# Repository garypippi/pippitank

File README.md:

# Pippitank

ラズパイ戦車制作プロジェクト

- 電源: 2S LiFe (タミヤ LF1100-6.6V)
- Raspberry Piでカメラ連携、リモート操作
- プッシュ型ソレノイドでBB弾発射

```
+----------+
| 2S LiFe  |
+----+-----+
     |
+----+-----------------+  UART  +-----------------------+
| pcb#pippitank-engine +--------+ pcb#pippitank-chassis |
+----+-----------------+        +----+--+-------+-------+
     |       |                       |  |       |
+-------+  +-------+      Dshot#2    |  |       | UART (Slip Ring)
| ESC#1 |  | ESC#2 |-----------------+  |       |
+----+--+  +-------+                    |    +----------------------+
     |                    Dshot#1       |    | pcb#pippitank-turret |
     +----------------------------------+    +----------------------+
                                                |
                                             ?? Planning... ??
```

## コマンド

### ビルド

```sh
cmake -S . -B build
cmake --build build
```

### RPi側

カメラストリーム配信。`--mode 1640:1232` はフル画角化のため（未指定だと中央クロップで約2.5倍ズームになる）:

```sh
rpicam-vid -t 0 --inline \
  --mode 1640:1232 \
  --width 640 --height 480 \
  --framerate 30 --listen -o tcp://0.0.0.0:8888
```

デーモン起動:

```sh
./build/src/pippitankd/pippitankd --listen 0.0.0.0:5000 --serial /dev/ttyS0
```

### ホスト側

操縦に使う入力デバイスの確認:

```sh
ls /dev/input/by-id
```

UI起動。`--log` は省略可（テレメトリCSVを記録する場合のみ）:

```sh
./build/src/pippitank-ui/pippitank-ui \
  --server pippitank:5000 \
  --video tcp://pippitank:8888 \
  --input /dev/input/event8 \
  --log logs/telemetry.csv
```

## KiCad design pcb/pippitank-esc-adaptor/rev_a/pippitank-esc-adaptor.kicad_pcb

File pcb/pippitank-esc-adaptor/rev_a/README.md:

**Known Issues**

1. U/V/Wのキャスタレーションでエッジカットがスルーホールの中心を通っていない

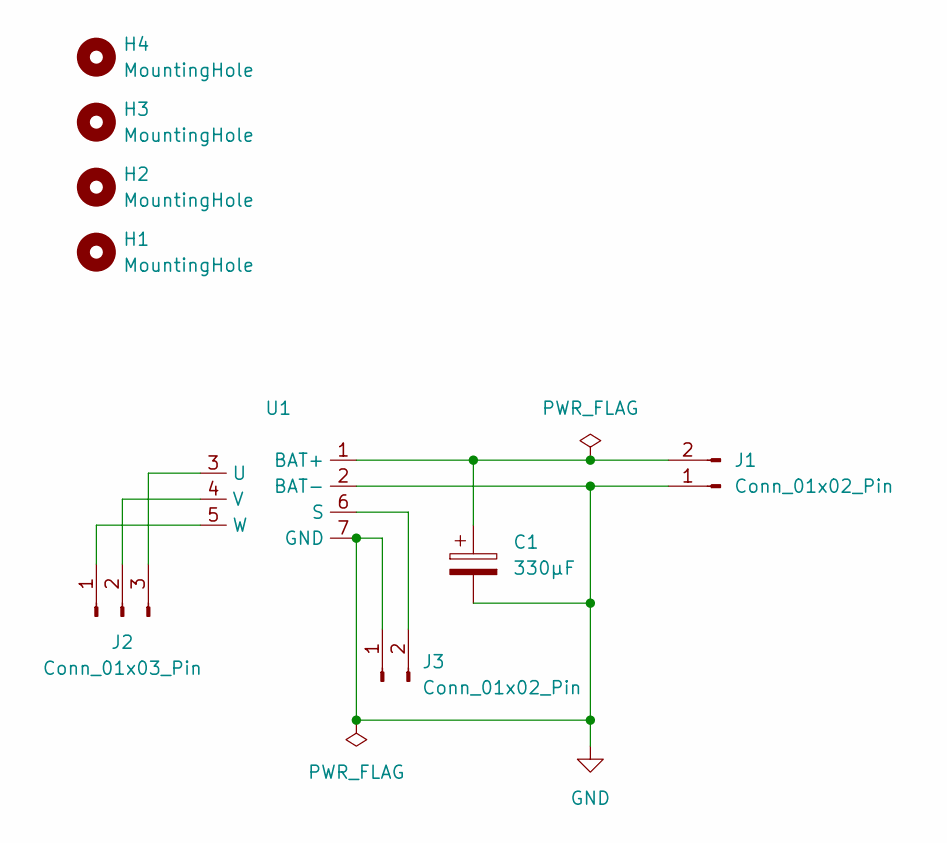
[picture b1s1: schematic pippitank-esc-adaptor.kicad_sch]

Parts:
C1: 330μF; CP_Radial_D10.0mm_P5.00mm
H1, H2, H3, H4: MountingHole; MountingHole_3.2mm_M3
J1: Conn_01x02_Pin; AMASS_XT30PW-M_1x02_P2.50mm_Horizontal
J2: Conn_01x03_Pin; AMASS_MR30PW-M_1x03_P3.50mm_Horizontal
J3: Conn_01x02_Pin; JST_XH_B2B-XH-A_1x02_P2.50mm_Vertical
U1: NOBRAND_ESC_ADAPTOR

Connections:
GND: C1.2, J1.1, J3.1, U1.2 (BAT-), U1.7 (GND)
unnamed: C1.1, J1.2, U1.1 (BAT+)
unnamed: J2.1, U1.5 (W)
unnamed: J2.2, U1.4 (V)
unnamed: J2.3, U1.3 (U)
unnamed: J3.2, U1.6 (S)

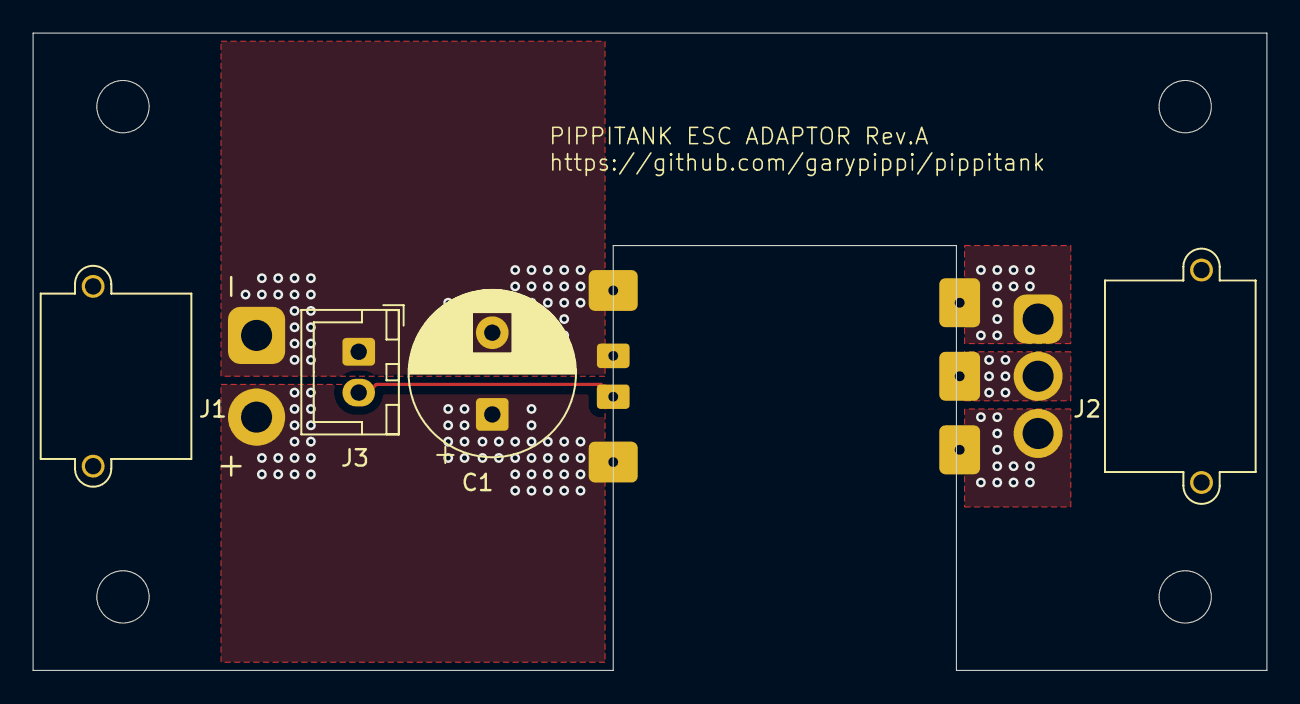
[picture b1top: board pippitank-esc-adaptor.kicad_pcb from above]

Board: 2 copper layers, 75.5 x 39.0 mm, 9 parts (1 on the bottom side), 6 nets.

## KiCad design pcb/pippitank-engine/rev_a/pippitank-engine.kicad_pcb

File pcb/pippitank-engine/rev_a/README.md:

**Known Issues**

1. バランスコネクタのGND,8.4Vが逆
    - JST_XH_3PIN Verticalを逆で実装すること
2. Nch-MOSFETのソースが浮いている
    - SWはON状態で固定すること

## 主要パーツ

- MCU: ATtiny1604
- Pch-MOSFET: TJ60S04M3L
- 電流測定用アンプ: LT6106CS5

## 設計根拠

電力想定

- 各ESCはMAX30A
- システムはMAX5A

## コネクタ

- XT60PW-M: 2S Li-Po
- XT60PW-M: ESC#1
- XT60PW-M: ESC#2
- XT30PW-M: システム#1
- XT30PW-M: システム#2
- JST_XH_3PIN: 2S Li-Po バランスコネクタ
- JST_XH_3PIN: UPDI
- JST_XH_4PIN: UART

## 電流測定 (ESC)

シャント抵抗は1W7mΩ ±5%を調達
並列数は4、 上限30Aとして

- 各抵抗の電流: 7.5A
- 各抵抗の電力: 0.394W
- 電圧降下@30A: 52.5mV
- 必要利得    : 20.95
- 測定誤差@30A: ±0.2A
- 測定誤差@10A: ±2.0%
- 測定誤差@05A: ±4.0%

ADC基準電圧は、精度を優先し1.1Vを使用する。
必要利得は

20.95 = 1100 / 52.5

利得は`ROUT/RIN`で設定する。
RINの範囲にはLT6106内部電流の制約がある。

> 内部電流の上限は1mA、30A時のセンス電圧52.5mVを流すには
> RIN ≥ 52.5mV / 1mA = 52.5Ω
> が必要。
> データシート条件から
> RIN ≤ 500Ω

よって

52.5Ω < RIN < 500Ω

- RIN=240Ω
- ROUT=4.7kΩ (Av≈19.58)
- 出力@30A=1.028V
- 実効FS≈32.1A

出力フィルタは2段LPF構成にする。

- 1段目(LT6106付近): ROUT(4.7kΩ) × COUT1(0.1μF) ≈ 338Hz
    - PWMノイズ(16〜32kHz)を発生源で大幅減衰（-33dB以上）
    - フィルタ後の出力インピーダンスが高周波で低くなり、配線のアンテナ化を抑制
- 2段目(ADC付近): Rs(100Ω) × COUT2(10nF) ≈ 160kHz
    - 長配線で新規に拾ったHFスパイク（FETスイッチング過渡、RF誘導）を叩き落とす
    - ATtiny1604のSAR ADC S/Hキャパへのローカル電荷供給も兼用

```
┌───────┬───────┬──────────────────────────────────────┐
│ 素子  │  値   │                 用途                 │
├───────┼───────┼──────────────────────────────────────┤
│ RIN   │ 240Ω  │ 入力抵抗                             │
├───────┼───────┼──────────────────────────────────────┤
│ ROUT  │ 4.7kΩ │ 出力抵抗（利得設定 兼 1段目LPFのR）  │
├───────┼───────┼──────────────────────────────────────┤
│ COUT1 │ 0.1μF │ ROUT並列、1段目LPFのC（LT6106直近）  │
├───────┼───────┼──────────────────────────────────────┤
│ Rs    │ 100Ω  │ 2段目LPFの直列R（配線途中〜ADC直前） │
├───────┼───────┼──────────────────────────────────────┤
│ COUT2 │ 10nF  │ 2段目LPFのC（ADC直近）               │
└───────┴───────┴──────────────────────────────────────┘
```

**実装時はケルビン接続**

## 電流測定 (システム)

車体、砲塔への電流測定。
負荷はRPi Zero W、RPi Camera、サーボx2、プッシュ型ソレノイド、各MCU

シャント抵抗は1W40mΩ ±1%を調達
並列数は2、 上限5Aとして

- 各抵抗の電流: 2.5A
- 各抵抗の電力: 0.25W (定格50%デレーティング)
- 電圧降下@5A: 100mV
- 必要利得    : 11.0
- 測定誤差@5A: ±1.0%
- 測定誤差@1A: ±5.0%

ADC基準電圧は、精度を優先し1.1Vを使用する。
必要利得は

11.0 = 1100 / 100

- RIN=240Ω
- ROUT=2.4kΩ (Av≈10.0) ※ 2.4kΩは調達しやすい

出力フィルタは2段LPF構成にする。

- 1段目(LT6106付近): ROUT(2.4kΩ) × COUT1(0.1μF) ≈ 663Hz
- 2段目(ADC付近): Rs(100Ω) × COUT2(10nF) ≈ 160kHz

```
┌───────┬───────┬──────────────────────────────────────┐
│ 素子  │  値   │                 用途                 │
├───────┼───────┼──────────────────────────────────────┤
│ RIN   │ 240Ω  │ 入力抵抗                             │
├───────┼───────┼──────────────────────────────────────┤
│ ROUT  │ 2.4kΩ │ 出力抵抗（利得設定 兼 1段目LPFのR）  │
├───────┼───────┼──────────────────────────────────────┤
│ COUT1 │ 0.1μF │ ROUT並列、1段目LPFのC（LT6106直近）  │
├───────┼───────┼──────────────────────────────────────┤
│ Rs    │ 100Ω  │ 2段目LPFの直列R（配線途中〜ADC直前） │
├───────┼───────┼──────────────────────────────────────┤
│ COUT2 │ 10nF  │ 2段目LPFのC（ADC直近）               │
└───────┴───────┴──────────────────────────────────────┘
```

**実装時はケルビン接続**

## 電圧測定

測定地点

1. BATバランス端子: セル#1
2. BAT(+) - BAT(-): 2 - 1 = セル#2電圧
3. post-MOSFETノード - BAT(-): ESC両系統への給電電圧 (Pch-MOSFET ON確認 + 電圧降下モニタ兼用)

抵抗分圧について、精度優先で内蔵基準電圧1.1Vを使用する
MAX8.4として

- (R1+R2)/R2 = 8.4 / 1.1 = 7.64
- R1/R2 = 6.64

R1 = 67kΩ (47kΩ + 20kΩ)
R2 = 10kΩ (8.4V時 1.091V、6.0V時 0.779V)

MAX4.2の場合は R1=47kΩ にすれば良い(4.2V時 0.737V)

LT6106の電流測定と同じく、2段LPF構成で配置する

```
Vin ── R1 ──┬──[配線]── Rs ──┬── ATtiny ADC
            │                │
            R2               C2(10nF)
            │                │
            ├── C1(0.1μF)    GND
            │
           GND
```

- R1, R2, C1 は信号源側に密集させる
  - R2 をMCU側に離すと配線区間が R1=67kΩ の高インピーダンスになり、ノイズを盛大に拾う
  - R1||R2 = 8.7kΩ を信号源側で確立し、低インピーダンス信号を配線に乗せる
- Rs（100Ω）は配線途中〜ADC直前（LT6106と同規格）
  - 2段目LPFの直列R、ADC入力保護
- C2=10nF はADC直近（LT6106のCOUT2と共用規格）
  - 配線で拾ったHFノイズをADC直前でシャント
  - ATtiny1604 SAR ADC のS/Hキャパ充電にも寄与

```
┌───────┬──────────┬──────────────────────────────────────┐
│ 素子  │   値     │               用途                   │
├───────┼──────────┼──────────────────────────────────────┤
│ R1    │ 67kΩ等   │ 分圧上段（信号源側）                 │
├───────┼──────────┼──────────────────────────────────────┤
│ R2    │ 10kΩ     │ 分圧下段（信号源側、R1とセット）     │
├───────┼──────────┼──────────────────────────────────────┤
│ C1    │ 0.1μF    │ R2並列、1段目LPF（信号源側）         │
├───────┼──────────┼──────────────────────────────────────┤
│ Rs    │ 100Ω     │ 2段目LPFの直列R（電流系と共用規格）  │
├───────┼──────────┼──────────────────────────────────────┤
│ C2    │ 10nF     │ 2段目LPF（ADC直近、電流系と共用規格）│
└───────┴──────────┴──────────────────────────────────────┘
```

## 基板温度測定

Pch-MOSFET および シャント抵抗の発熱監視用に NTCサーミスタを1点実装する。

- サーミスタ: NTC 47kΩ ±5% B=4050K ±3% (TDK NTH5G20P40B473J、2012)
- プルアップ: 47kΩ ±5% (NTC R25と対称にして25°C付近の感度最大化、±5%は調達制約・表示用途なら実用上問題なし)
- フィルタ: 2段LPF構成
- ADC参照: VDD(5V) ※この1chのみ、他chは1.1V内部参照のまま

```
VCC(5V) ── R_pu 47kΩ ──┬──[配線]── Rs ──┬── ATtiny ADC (PA7)
                       │                │
                       NTC 47kΩ         C2 (10nF)
                       │                │
                       ├── C1 (0.1μF)   GND
                       │
                       GND
```

温度 vs ADCコード (VDD=5V, 10bit, B=4050K):

```
┌──────┬─────────┬────────┬─────────┐
│ 温度 │ NTC抵抗 │  電圧  │ ADCコード │
├──────┼─────────┼────────┼─────────┤
│ 0°C  │ 163kΩ   │ 3.88V  │  795    │
│ 25°C │ 47kΩ    │ 2.50V  │  512    │
│ 60°C │ 11.3kΩ  │ 0.97V  │  198    │
│ 85°C │ 4.84kΩ  │ 0.47V  │   96    │
│100°C │ 3.06kΩ  │ 0.31V  │   63    │
└──────┴─────────┴────────┴─────────┘
```

Pch-MOSFET裏面の銅箔ベタに密着させ、シャント抵抗発熱も熱結合で捕捉する。
シャットダウン閾値はマージンを取り ADCコード 110 (公称 82°C) 付近で発動、
最悪ケース (B+3%, R25+5%) でも実温度 85°C を超える前に遮断される想定とする。

```
┌───────┬──────────┬─────────────────────────────────────┐
│ 素子  │   値     │               用途                  │
├───────┼──────────┼─────────────────────────────────────┤
│ R_pu  │ 47kΩ ±5% │ プルアップ（信号源側）              │
├───────┼──────────┼─────────────────────────────────────┤
│ NTC   │ 47kΩ     │ NTH5G20P40B473J（信号源側）         │
├───────┼──────────┼─────────────────────────────────────┤
│ C1    │ 0.1μF    │ 1段目LPF（信号源側、NTC並列）       │
├───────┼──────────┼─────────────────────────────────────┤
│ Rs    │ 100Ω     │ 2段目LPFの直列R（全系統共用規格）   │
├───────┼──────────┼─────────────────────────────────────┤
│ C2    │ 10nF     │ 2段目LPF（ADC直近、全系統共用規格） │
└───────┴──────────┴─────────────────────────────────────┘
```

## ATtiny1604

ATtiny1604の消費電力は小さいので、BAT接続時は常に稼働させる

```
BAT(+) ---+---------- (VIN) AP7375 (VOUT) -+--- (A)▷|(K) --- VCC rail --- ATtiny1604
          |                  |             |         D2                   UPDI 5V pin
          | CIN=1μF          |             |
          |                  |             | COUT=10μF
BAT(-) ---+------------------+-------------+
```

- LDO: AP7375(5V300mA)
- 内蔵オシレータ使用
- UPDI引き出し
- 逆流防止ショットキー D2

BAT未接続状態でもArduino Uno経由でUPDI書き込みできるよう、AP7375出力とVCC rail間にショットキーダイオードを挿入する。

- 型番: RB160M-30TR (ROHM, 30V 1A)
- パッケージ: SOD-123F (PMDS、フラットリード)
- VF: 0.43V @ 1A、実動作の~10mA負荷では ~0.2V
- VCC rail電圧: 5.0V - 0.2V ≈ 4.8V（ATtiny動作範囲1.8-5.5V内）

```
AP7375 --+-- (A)▷|(K) ----+----- ATtiny VCC (pin 1)
         |      D2         |
         |                 +--- UPDI header 5V pin
         C2=10μF           |
         |                 C_bypass=0.1μF
        GND               GND
```

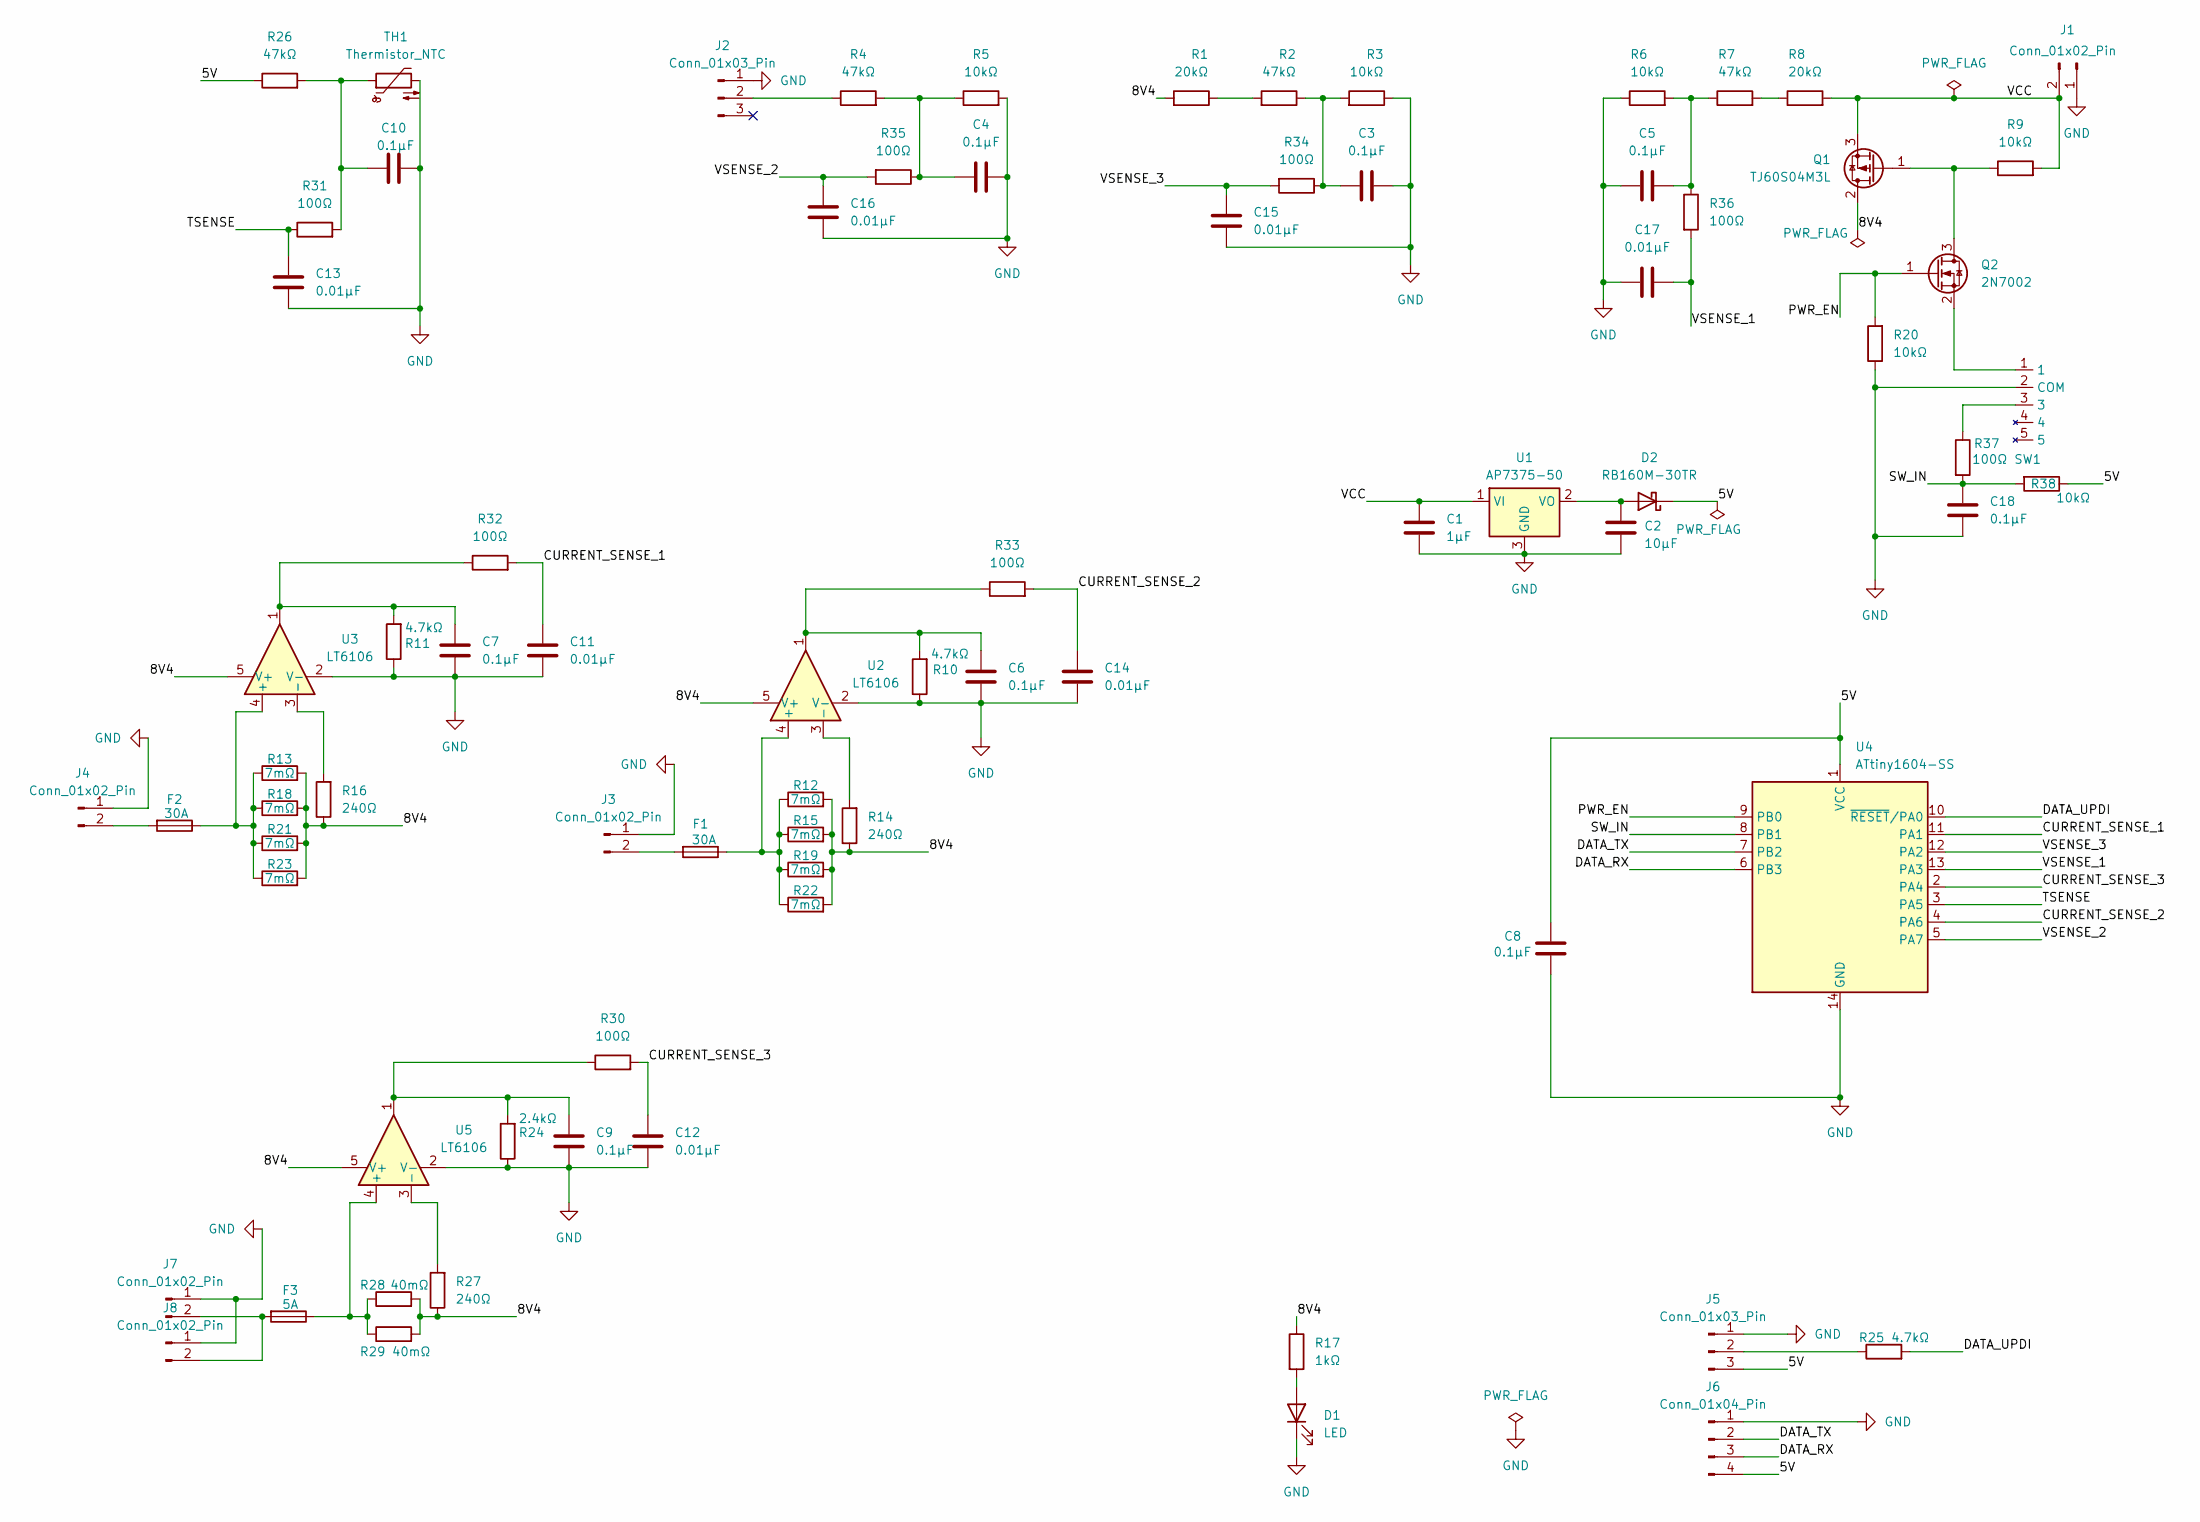
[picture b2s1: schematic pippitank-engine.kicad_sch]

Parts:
C1: 1μF; R_0603_1608Metric_Pad0.98x0.95mm_HandSolder
C2: 10μF; R_0805_2012Metric_Pad1.20x1.40mm_HandSolder
C3, C4, C5, C6, C7, C8, C9, C10, C18: 0.1μF; R_0603_1608Metric_Pad0.98x0.95mm_HandSolder
C11, C12, C13, C14, C15, C16, C17: 0.01μF; R_0603_1608Metric_Pad0.98x0.95mm_HandSolder
D1: LED; LED_0603_1608Metric_Pad1.05x0.95mm_HandSolder
D2: RB160M-30TR; D_SOD-123F
F1, F2: 30A; Keystone_3557_15
F3: 5A; Keystone_3557_15
J1, J3, J4: Conn_01x02_Pin; AMASS_XT60PW-M_1x02_P7.20mm_Horizontal
J2: Conn_01x03_Pin; JST_XH_S3B-XH-A_1x03_P2.50mm_Horizontal
J5: Conn_01x03_Pin; JST_XH_B3B-XH-A_1x03_P2.50mm_Vertical
J6: Conn_01x04_Pin; JST_XH_S4B-XH-A_1x04_P2.50mm_Horizontal
J7, J8: Conn_01x02_Pin; AMASS_XT30PW-M_1x02_P2.50mm_Horizontal
Q1: TJ60S04M3L; TO-252-3_TabPin2
Q2: 2N7002; SOT-23
R1, R8: 20kΩ; R_0603_1608Metric_Pad0.98x0.95mm_HandSolder
R2, R4, R7, R26: 47kΩ; R_0603_1608Metric_Pad0.98x0.95mm_HandSolder
R3, R5, R6, R9, R20, R38: 10kΩ; R_0603_1608Metric_Pad0.98x0.95mm_HandSolder
R10, R11, R25: 4.7kΩ; R_0603_1608Metric_Pad0.98x0.95mm_HandSolder
R12, R13, R15, R18, R19, R21, R22, R23: 7mΩ; R_2512_6332Metric
R14, R16, R27: 240Ω; R_0603_1608Metric_Pad0.98x0.95mm_HandSolder
R17: 1kΩ; R_0603_1608Metric_Pad0.98x0.95mm_HandSolder
R24: 2.4kΩ; R_0603_1608Metric_Pad0.98x0.95mm_HandSolder
R28, R29: 40mΩ; R_2512_6332Metric
R30, R31, R32, R33, R34, R35, R36, R37: 100Ω; R_0603_1608Metric_Pad0.98x0.95mm_HandSolder
SW1: SSAJ120100
TH1: Thermistor_NTC; R_0805_2012Metric_Pad1.20x1.40mm_HandSolder
U1: AP7375-50; SOT-23_Handsoldering
U2, U3, U5: LT6106; SOT-23-5_HandSoldering
U4: ATtiny1604-SS; SOIC-14_3.9x8.7mm_P1.27mm

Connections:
/5V: C8.2, D2.1 (K), J5.3, J6.4, R26.1, R38.1, U4.1 (VCC)
/8V4: Q1.2 (D), R1.2, R12.2, R13.2, R14.1, R15.2, R16.1, R17.1, R18.2, R19.2, R21.2, R22.2, R23.2, R27.1, R28.2, R29.2, U2.5 (V+), U3.5 (V+), U5.5 (V+)
/CURRENT_SENSE_1: C11.1, R32.2, U4.11 (PA1)
/CURRENT_SENSE_2: C14.1, R33.2, U4.4 (PA6)
/CURRENT_SENSE_3: C12.1, R30.2, U4.2 (PA4)
/DATA_RX: J6.3, U4.6 (PB3)
/DATA_TX: J6.2, U4.7 (PB2)
/DATA_UPDI: R25.2, U4.10 (~RESET/PA0)
/PWR_EN: Q2.1 (G), R20.2, U4.9 (PB0)
/SW_IN: C18.2, R37.2, R38.2, U4.8 (PB1)
/TSENSE: C13.1, R31.1, U4.3 (PA5)
/VCC: C1.1, J1.2, Q1.3 (S), R8.2, R9.2, U1.1 (VI)
/VSENSE_1: C17.1, R36.2, U4.13 (PA3)
/VSENSE_2: C16.2, R35.2, U4.5 (PA7)
/VSENSE_3: C15.2, R34.2, U4.12 (PA2)
GND: C1.2, C2.2, C3.2, C4.2, C5.2, C6.2, C7.2, C8.1, C9.2, C10.1, C11.2, C12.2, C13.2, C14.2, C15.1, C16.1, C17.2, C18.1, D1.1 (K), J1.1, J2.1, J3.1, J4.1, J5.1, J6.1, J7.1, J8.1, R3.1, R5.2, R6.1, R10.1, R11.1, R20.1, R24.1, SW1.2 (COM), TH1.2, U1.3 (GND), U2.2 (V-), U3.2 (V-), U4.14 (GND), U5.2 (V-)
unnamed: C3.1, R2.1, R3.2, R34.1
unnamed: C4.1, R4.2, R5.1, R35.1
unnamed: C5.1, R6.2, R7.1, R36.1
unnamed: C6.1, R10.2, R33.1, U2.1
unnamed: C7.1, R11.2, R32.1, U3.1
unnamed: C9.1, R24.2, R30.1, U5.1
unnamed: C10.2, R26.2, R31.2, TH1.1
unnamed: D1.2 (A), R17.2
unnamed: C2.1, D2.2 (A), U1.2 (VO)
unnamed: J2.2, R4.1
unnamed: F1.2, J3.2
unnamed: F2.2, J4.2
unnamed: J5.2, R25.1
unnamed: F3.2, J7.2, J8.2
unnamed: Q1.1 (G), Q2.3 (D), R9.1
unnamed: Q2.2 (S), SW1.1
unnamed: R1.1, R2.2
unnamed: R7.2, R8.1
unnamed: R37.1, SW1.3
unnamed: F1.1, R12.1, R15.1, R19.1, R22.1, U2.4 (+)
unnamed: R14.2, U2.3 (-)
unnamed: F2.1, R13.1, R18.1, R21.1, R23.1, U3.4 (+)
unnamed: R16.2, U3.3 (-)
unnamed: F3.1, R28.1, R29.1, U5.4 (+)
unnamed: R27.2, U5.3 (-)

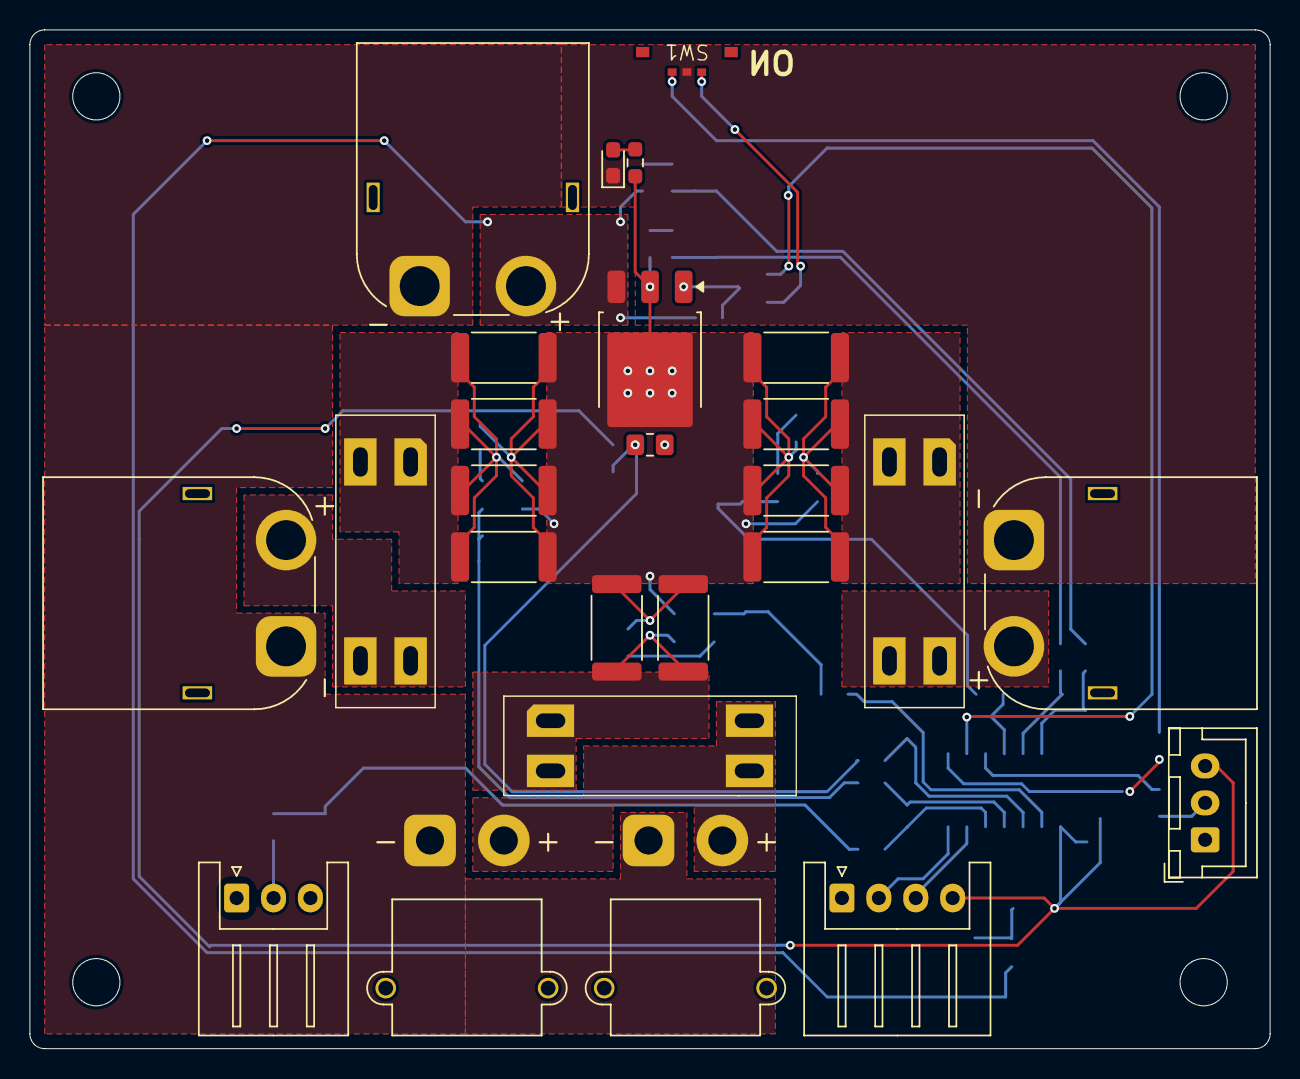
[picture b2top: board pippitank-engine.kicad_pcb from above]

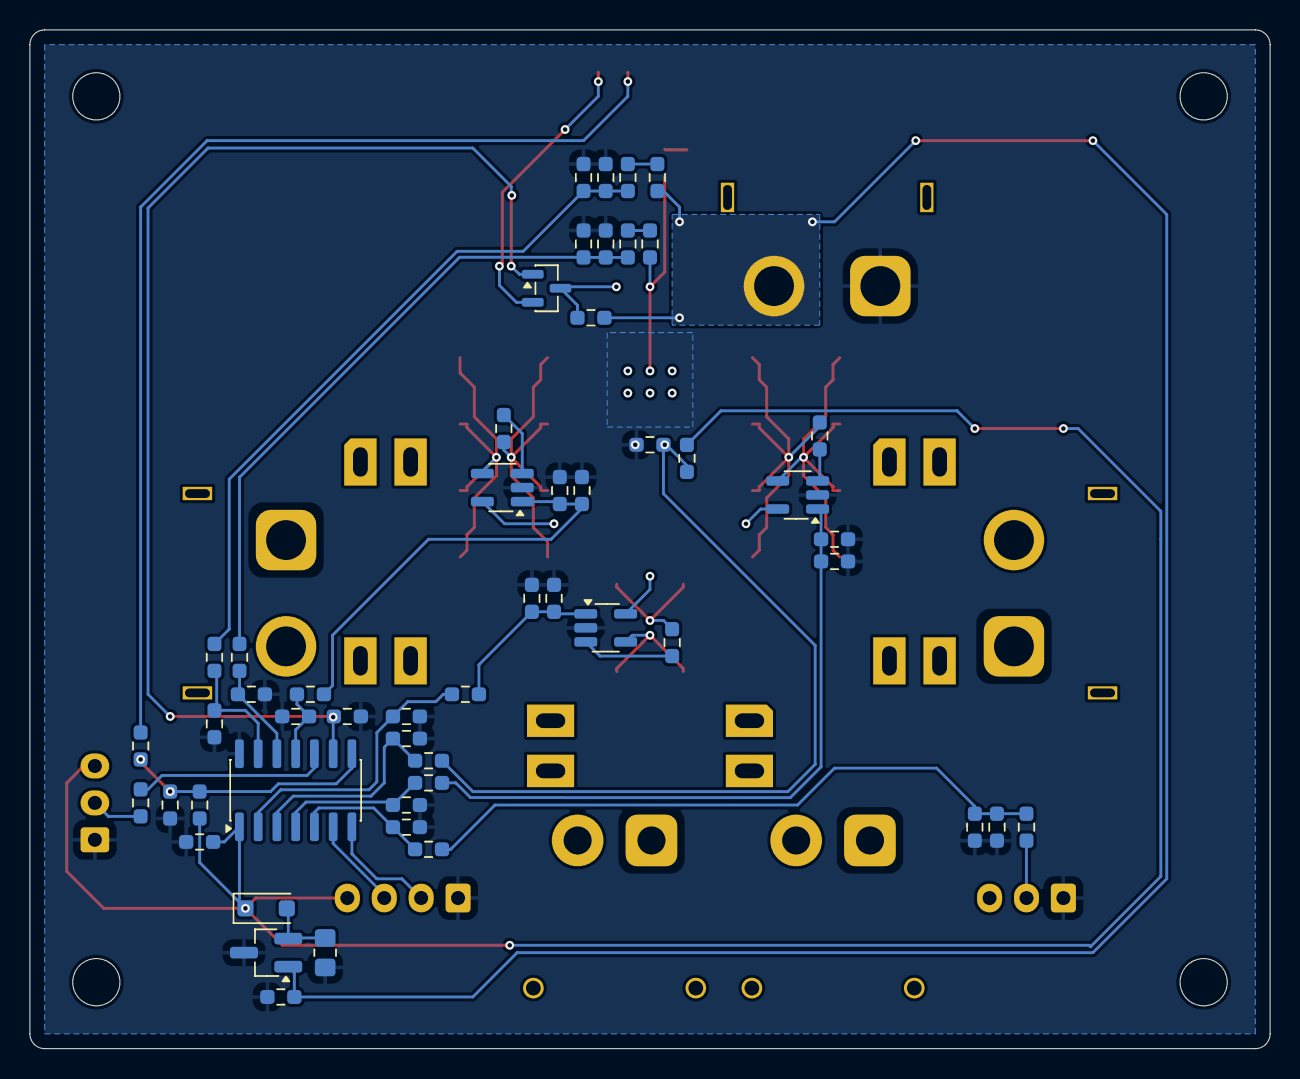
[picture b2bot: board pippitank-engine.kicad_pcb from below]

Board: 2 copper layers, 84.0 x 69.0 mm, 78 parts (52 on the bottom side), 41 nets.

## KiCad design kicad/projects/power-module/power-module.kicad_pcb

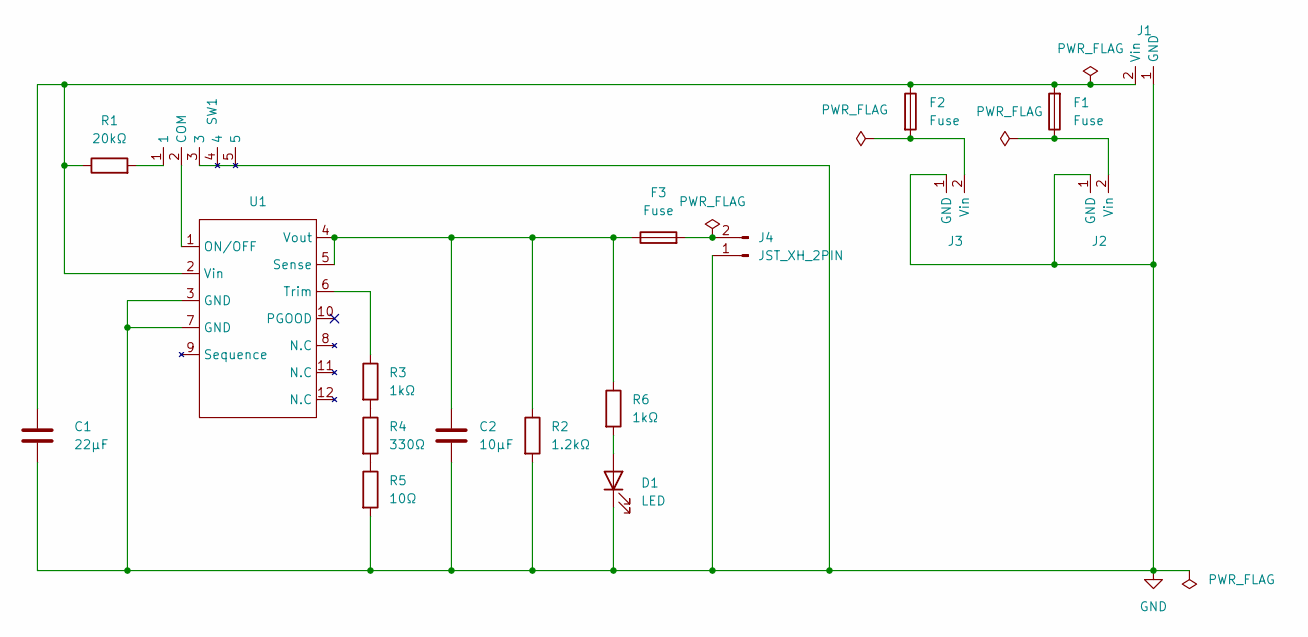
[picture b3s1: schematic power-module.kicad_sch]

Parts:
C1: 22μF; C_1210_3225Metric
C2: 10μF; C_0805_2012Metric
D1: LED; LED_0603_1608Metric
F1, F2, F3: Fuse; Keystone_3557_15
J1, J2, J3: AMASS_XT60PW-M_1x02_P7.20mm_Horizontal
J4: JST_XH_2PIN; JST_XH_B2B-XH-A_1x02_P2.50mm_Vertical
R1: 20kΩ; R_0603_1608Metric
R2: 1.2kΩ; R_0603_1608Metric
R3, R6: 1kΩ; R_0603_1608Metric
R4: 330Ω; R_0603_1608Metric
R5: 10Ω; R_0603_1608Metric
SW1: SSAJ120100
U1: OKL_T6_W12

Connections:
GND: C1.2, C2.2, D1.1 (K), J1.1 (GND), J2.1 (GND), J3.1 (GND), J4.1, R2.2, R5.2, SW1.3, U1.3 (GND), U1.7 (GND)
unnamed: D1.2 (A), R6.2
unnamed: C1.1, F1.2, F2.1, J1.2 (Vin), R1.1, U1.2 (Vin)
unnamed: F1.1, J2.2 (Vin)
unnamed: F2.2, J3.2 (Vin)
unnamed: F3.2, J4.2
unnamed: R1.2, SW1.1
unnamed: R3.2, R4.1
unnamed: R4.2, R5.1
unnamed: SW1.2 (COM), U1.1 (ON/OFF)
unnamed: C2.1, F3.1, R2.1, R6.1, U1.4 (Vout), U1.5 (Sense)
unnamed: R3.1, U1.6 (Trim)

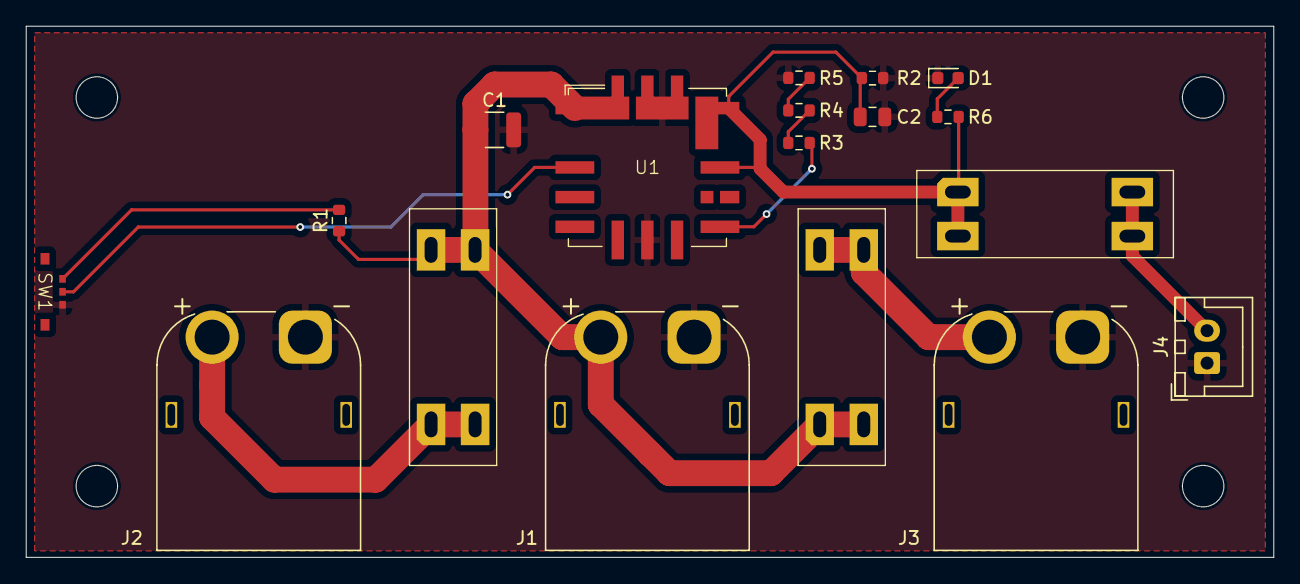
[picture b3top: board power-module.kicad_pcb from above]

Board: 2 copper layers, 96.3 x 41.0 mm, 18 parts (0 on the bottom side), 12 nets.

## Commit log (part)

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2020-10-28 ('_')
2020-10-29 ccls
2020-10-29 README
2020-10-29 Manually send pulse to Arduino
2020-10-29 Mention requirement
2020-11-02 Unity initial setups (2D)
2026-04-04 Add LICENSE
2026-04-04 Add .clangd
2026-04-04 Add CLAUDE.md
2026-04-04 電源モジュールのCAD試作
2026-04-04 Add .gitignore
2026-04-04 Add Makefile
2026-04-04 モーターx1の制御プログラムを試作
2026-04-04 Remove .ccls
2026-04-04 README.md 部品表の修正
2026-04-11 ESCx1制御のRPi側
2026-04-11 ホストマシンで実行する用にMakefile修正
2026-04-12 コードスタイルの統一
2026-04-12 後退コマンドを追加
2026-04-13 Rename kicad -> pcb
2026-05-02 SSAJ120100のフットプリント修正
2026-05-03 pippitank-engine REV_A
2026-05-03 Update gitignore
2026-05-03 Remove unused pcb designe
2026-05-03 Rename some files in src/
2026-05-03 Update Makefile
2026-05-12 Add pippitank-esc-adaptor rev_a
2026-05-12 pippitank-engineのエミュレータ作成、protocol.hのcpp移行
2026-05-12 Add ESC adaptor symbol & footprint
